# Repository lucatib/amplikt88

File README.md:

# amplikt88

Mono KT88 push-pull power amplifier, ultralinear, class AB, fixed bias. KiCad 10 project: schematic on two sheets ([PDF](amplikt88.pdf)), two-layer board.

## Circuit

- **Input:** ECC83 triode, 470k anode load, unbypassed cathode (R4 1.5k) takes the global feedback.
- **Driver:** ECC83 long-tailed pair, direct coupled to the input stage as in the Mullard 5-10/5-20. The tail is the spare V1 triode as a 2.33 mA current sink fed from BIAS_CCS. Lag R29 15k + C17 180p at V1's anode.
- **Output:** 2x KT88, coupled through C7/C8 0.47 µF 630 V, screens on the transformer's 40 % UL taps, 200k grid resistors, bias trimmers RV1/RV2.
- **Feedback:** 180k ∥ 12 pF from the speaker terminal to V1's cathode, about 17 dB.
- **Supply** ([power sheet](docs/schematic/power.svg)): 330 V bridge, C-L-C to 450 V B+, decoupled B_DRV and B_V1, bridge-rectified −65 V bias rail, 6.3 V heaters.

Design studies: [spare-triode comparison](docs/research/amplikt88-innovation/spare-triode-comparison.md), [output transformer](docs/output-transformer.md), [innovation review](docs/amplikt88-innovation-review.md), [design notes](docs/valve-design-notes.md).

## Simulation

`python3 spice/simulate.py` exports the netlist with `kicad-cli` and runs ngspice ([models](spice/amplikt88.lib)); `spice/plot.py` redraws the plots. Ideal 450 V and −65 V sources, 8 Ω load.

| | |
|---|---|
| Idle | 60 mA per KT88 (grid −55.8 V) |
| Loop gain, 1 kHz | 17.3 dB |
| Margins, top / bottom | 102° / 28 dB, 56° / 26 dB |
| Bandwidth (−3 dB) | 2.9 Hz – 33 kHz |
| THD, 37 W | 0.078 % at 1 kHz, 0.51 % at 10 kHz |
| Power at 1 % THD | 60 W |

The valve models are fits to the [datasheets](docs/datasheets/README.md) (5–12 % rms); use the numbers to compare variants, not as measurements.

## Board

218.67 × 98.0 mm, two layers, mounted vertically on an L bracket. Five M4 holes: four corners and H2 on the centre line.

| Top | Bottom |
|---|---|
|  |  |

- **F.Cu** carries the signal and power nets. **B.Cu** carries the ground star from J4 pin 6, plus short jumpers for blocked or low-voltage nets (VBIAS_NEG, heaters, LTP_A1, G3_IN, G4_IN, V2_G2 to C16). Two vias, 1.6/0.8 mm.
- **Clearance to ground and mounting holes:** 5 mm for HV, 6.3 mm for UL taps and screens, 8 mm for KT88 anodes. HV nets keep 2.5 mm from each other. Rules are in [amplikt88.kicad_dru](amplikt88.kicad_dru).
- **Milled slots (0.8 mm, Edge.Cuts):** three slots lengthen the surface path where high and low voltage sit close: an L at V3 between R17.2 (UL tap) and C7.2 (G3_IN), an L under R12 at V4 (G4_IN), and a straight one in J4 between B_V1 (pin 3) and VBIAS_NEG (pin 4). The `FESSURA_*` rule areas in the DRC rules mark them. Ask the board house for milled slots, not V-score.
- **Heaters:** V1 + V2 go to JH2, V3 to JH3, V4 to JH4. Each pair is wired separately to the 6.3 V winding, so DRC lists 4 unconnected heater items by design.
- **DRC:** no errors. Besides the 4 heater items above, it shows 3 silkscreen warnings where the milled slots cut the outlines of R12, R17 and J4, which the board house trims. One exclusion: R19's courtyard sits 0.37 mm from V3's, against the 4 mm glass rule.
- **V4 corner:** /G2_V4 runs between V4 pin 5 (G1) and the /OT_A2 track, with 6.3 mm creepage to the grid and 2.5 mm clearance to the anode. R18 sits clear of the bias network so /OT_A2 keeps 8 mm from RV2, R12 and BIAS_B.
- **Off-board connections:** TR2 to the output transformer, J4 to the supply, J3 to the speaker, J2 for the input.
- **Back side:** C7, C8 and C16 (film caps, WIMA MKS 4 630 VDC) sit on the back, away from the KT88 glass. C7 and C8 (0.47 µF, MKS4J034706A) are 9 × 19 × 31.5 mm, C16 (1 µF, MKS4J041006B) 11 × 21 × 31.5 mm, all on a 27.5 mm pitch. C16 lies along the bottom edge between JH3 and R10 (its body comes to about 0.3 mm from the edge on the back): /V2_G2 reaches it from R10 on B.Cu, its ground end joins the star at R19.

## Before building

Nothing has been measured on hardware. Check:
- **Transformers:**
  - Output: 4 kΩ plate-to-plate, 40 % UL taps, 8 Ω, 70 W ([spec](docs/output-transformer.md)).
  - Power: toroidal, wound to order (about 200 VA): 230 V 50 Hz primary; HV 330 V rms at full load, 500 mA AC (about 300 mA DC in a winder's capacitor-input rating); heaters 6.3 V / 4.5 A; bias 60 V / 100 mA; electrostatic screen between primary and secondaries; regulation 5 % or better; EN 61558.
  - Inrush: F1 is a slow-blow T2A (high I²t). If it blows at switch-on, add a soft-start (NTC in series with the primary, shorted by a relay after a second or two) rather than a bigger fuse.
  - Choke: 5 H / 300 mA.
- **Secondary phase:** wire the secondary in phase with the input. If it oscillates, swap the leads.
- **Bias:** turn both trimmers to most negative before power-up, then set 60 mA per KT88 (60 mV across the 1 Ω cathode resistors). Stay below 75 mA.
- **Sensitivity:** 0.16 V rms in gives 37 W. Fit a volume control.

- **Capacitor voltages:** C7 and C8 carry about 380 V DC at idle (LTP anode 325 V, KT88 grid −56 V) and up to about 590 V at a cold start with high mains, when V2 does not conduct yet and its anodes sit at the unloaded B+. C16 follows the LTP grid, which also rises towards B_V1 before V1 conducts. Use parts rated 630 VDC or more for all three.

**Danger:** B+ is 450 V and the capacitors hold their charge after power-off. Measure before touching.

## References

- Mullard, [*Circuits for Audio Amplifiers*](https://www.worldradiohistory.com/BOOKSHELF-ARH/Technology/Technology-General/Mullard%20Circuits%20For%20Audio%20Amplifiers.pdf), 1959: the 5-20 and 5-10 driver topology.
- G.E.C., [*An Approach to Audio Frequency Amplifier Design*](https://archive.org/details/An_Approach_to_Audio_Frequency_Amplifier_Design_G.E._Valve-Electronics_Dept._195), 1957: KT88 fixed-bias UL amplifiers.
- Radiotron Designer's Handbook, Valley–Wallman, Williamson, Morgan Jones: local copies and links in [docs/references](docs/references/README.md).
- Valve datasheets: [docs/datasheets](docs/datasheets/README.md).

[License](LICENSE)

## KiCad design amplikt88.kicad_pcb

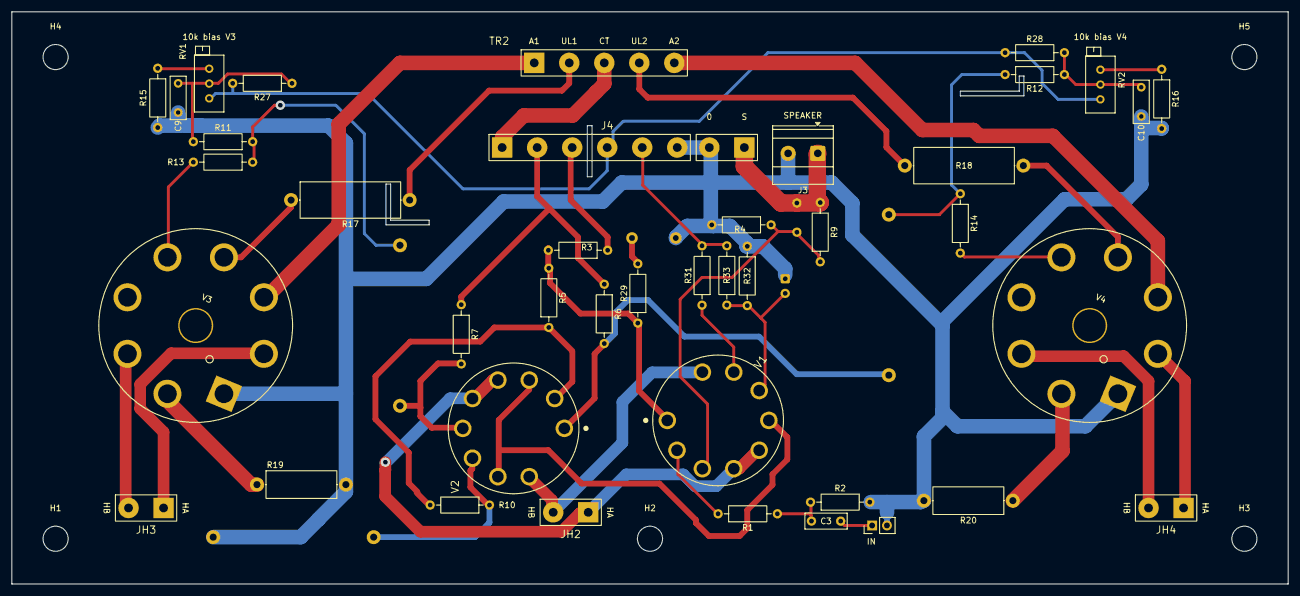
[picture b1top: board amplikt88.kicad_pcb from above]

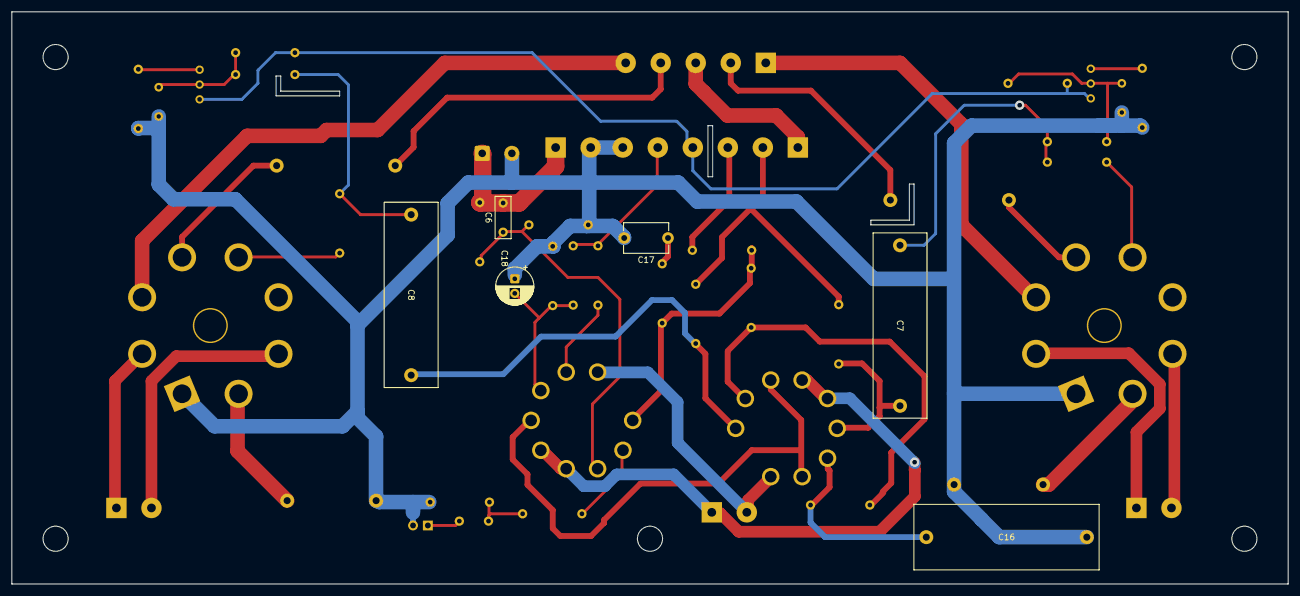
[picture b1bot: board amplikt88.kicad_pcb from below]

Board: 2 copper layers, 218.7 x 98.0 mm, 52 parts (6 on the bottom side), 38 nets.

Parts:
C3: 100n; C_Disc_D7.0mm_W2.5mm_P5.00mm
C6: 12p; C_Disc_D7.0mm_W2.5mm_P5.00mm
C7, C8: 0.47u 630V; C_Rect_L31.5mm_W9.0mm_P27.50mm_MKS4
C9, C10: 1u 100V; C_Rect_L7.2mm_W2.5mm_P5.00mm
C16: 1u 630V; C_Rect_L31.5mm_W11.0mm_P27.50mm_MKS4
C17: 180p 500V C0G; C_Disc_D7.5mm_W5.0mm_P7.50mm
C18: 10u 100V; CP_Radial_D6.3mm_P2.50mm
H1, H2, H3, H4, H5: M4; MountingHole_4.3mm_M4
J2: IN; PinHeader_1x02_P2.54mm_Vertical
J3: SPEAKER; TerminalBlock_Phoenix_MKDS-1,5-2-5.08_1x02_P5.08mm_Horizont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
J4: OFFBOARD SUPPLY; Supply_6
JH2: HEATER V1V2; Heater_2
JH3: HEATER V3; Heater_2
JH4: HEATER V4; Heater_2
R1, R5: 1k; R_Axial_DIN0207_L6.3mm_D2.5mm_P10.16mm_Horizontal
R2, R3: 470k; R_Axial_DIN0207_L6.3mm_D2.5mm_P10.16mm_Horizontal
R4: 1.5k; R_Axial_DIN0207_L6.3mm_D2.5mm_P10.16mm_Horizontal
R6, R7: 100k; R_Axial_DIN0207_L6.3mm_D2.5mm_P10.16mm_Horizontal
R9: 180k; R_Axial_DIN0207_L6.3mm_D2.5mm_P10.16mm_Horizontal
R10: 1.8M; R_Axial_DIN0207_L6.3mm_D2.5mm_P10.16mm_Horizontal
R11, R12: 200k; R_Axial_DIN0207_L6.3mm_D2.5mm_P10.16mm_Horizontal
R13, R14: 5k; R_Axial_DIN0207_L6.3mm_D2.5mm_P10.16mm_Horizontal
R15, R16: 27k; R_Axial_DIN0207_L6.3mm_D2.5mm_P10.16mm_Horizontal
R17, R18: 470R 2W; R_Axial_DIN0617_L17.0mm_D6.0mm_P20.32mm_Horizontal
R19, R20: 1R 1W; R_Axial_DIN0414_L11.9mm_D4.5mm_P15.24mm_Horizontal
R27, R28: 220k; R_Axial_DIN0207_L6.3mm_D2.5mm_P10.16mm_Horizontal
R29: 15k; R_Axial_DIN0207_L6.3mm_D2.5mm_P10.16mm_Horizontal
R31: 13k; R_Axial_DIN0207_L6.3mm_D2.5mm_P10.16mm_Horizontal
R32: 604k 1%; R_Axial_DIN0207_L6.3mm_D2.5mm_P10.16mm_Horizontal
R33: 392k 1%; R_Axial_DIN0207_L6.3mm_D2.5mm_P10.16mm_Horizontal
RV1: 10k bias V3; Potentiometer_Bourns_3296X_Horizontal
RV2: 10k bias V4; Potentiometer_Bourns_3296X_Horizontal
TR2: OT 4k a-a UL 70W; OT_7
V1, V2: ECC83; Valve_Noval_ECC83
V3, V4: KT88; Valve_Octal_KT88

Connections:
/BA_LO: R15.1, RV1.3
/BB_LO: R16.1, RV2.3
/BIAS_A: C9.1, R11.2, R27.1, RV1.2
/BIAS_B: C10.1, R12.2, R28.1, RV2.2
/CCS_G: C18.2, R32.1, R33.1, V1.7 (G)
/G2_V3: R17.1, V3.4 (G2)
/G2_V4: R18.1, V4.4 (G2)
/G3_IN: C7.2, R11.1, R13.1
/G4_IN: C8.2, R12.1, R14.1
/IN_C: C3.2, R1.1, R2.1
/IN_RAW: C3.1, J2.1
/LAG_STEP: C17.1, R29.2
/LTP_A1: C8.1, R6.2, V2.1 (A)
/LTP_A2: C7.1, R7.2, V2.6 (A)
/LTP_G1: R5.2, R10.2, V2.2 (G)
/LTP_K: V1.6 (A), V2.3 (K), V2.8 (K)
/OT_A1: TR2.1 (A1), V3.3 (A)
/OT_A2: TR2.5 (A2), V4.3 (A)
/OT_S_HI: C6.2, J3.1, R9.2, TR2.6 (S_HI)
/OT_UL1: R17.2, TR2.2 (UL1)
/OT_UL2: R18.2, TR2.4 (UL2)
/V1_A: R3.2, R5.1, R29.1, V1.1 (A)
/V1_G: R1.2, V1.2 (G)
/V1_K: C6.1, R4.1, R9.1, V1.3 (K)
/V2_G2: C16.1, R10.1, V2.7 (G)
/V3_G1: R13.2, V3.5 (G1)
/V3_K: R19.1, V3.8 (K)
/V4_G1: R14.2, V4.5 (G1)
/V4_K: R20.1, V4.8 (K)
BIAS_CCS: J4.5, R31.2, R33.2
B_DRV: J4.2, R6.1, R7.1
B_PLUS: J4.1, TR2.3 (CT)
B_V1: J4.3, R3.1
GND: C9.2, C10.2, C16.2, C17.2, C18.1, J2.2, J3.2, J4.6, R2.2, R4.2, R15.2, R16.2, R19.2, R20.2, R32.2, TR2.7 (S_LO), V3.1 (S), V4.1 (S)
HEATER_A: JH2.1, JH3.1, JH4.1, V1.4 (F1), V1.5 (F1), V2.4 (F1), V2.5 (F1), V3.2 (H), V4.2 (H)
HEATER_B: JH2.2, JH3.2, JH4.2, V1.9 (F2), V2.9 (F2), V3.7 (H), V4.7 (H)
unnamed: R31.1, V1.8 (K)
VBIAS_NEG: J4.4, R27.2, R28.2, RV1.1, RV2.1
